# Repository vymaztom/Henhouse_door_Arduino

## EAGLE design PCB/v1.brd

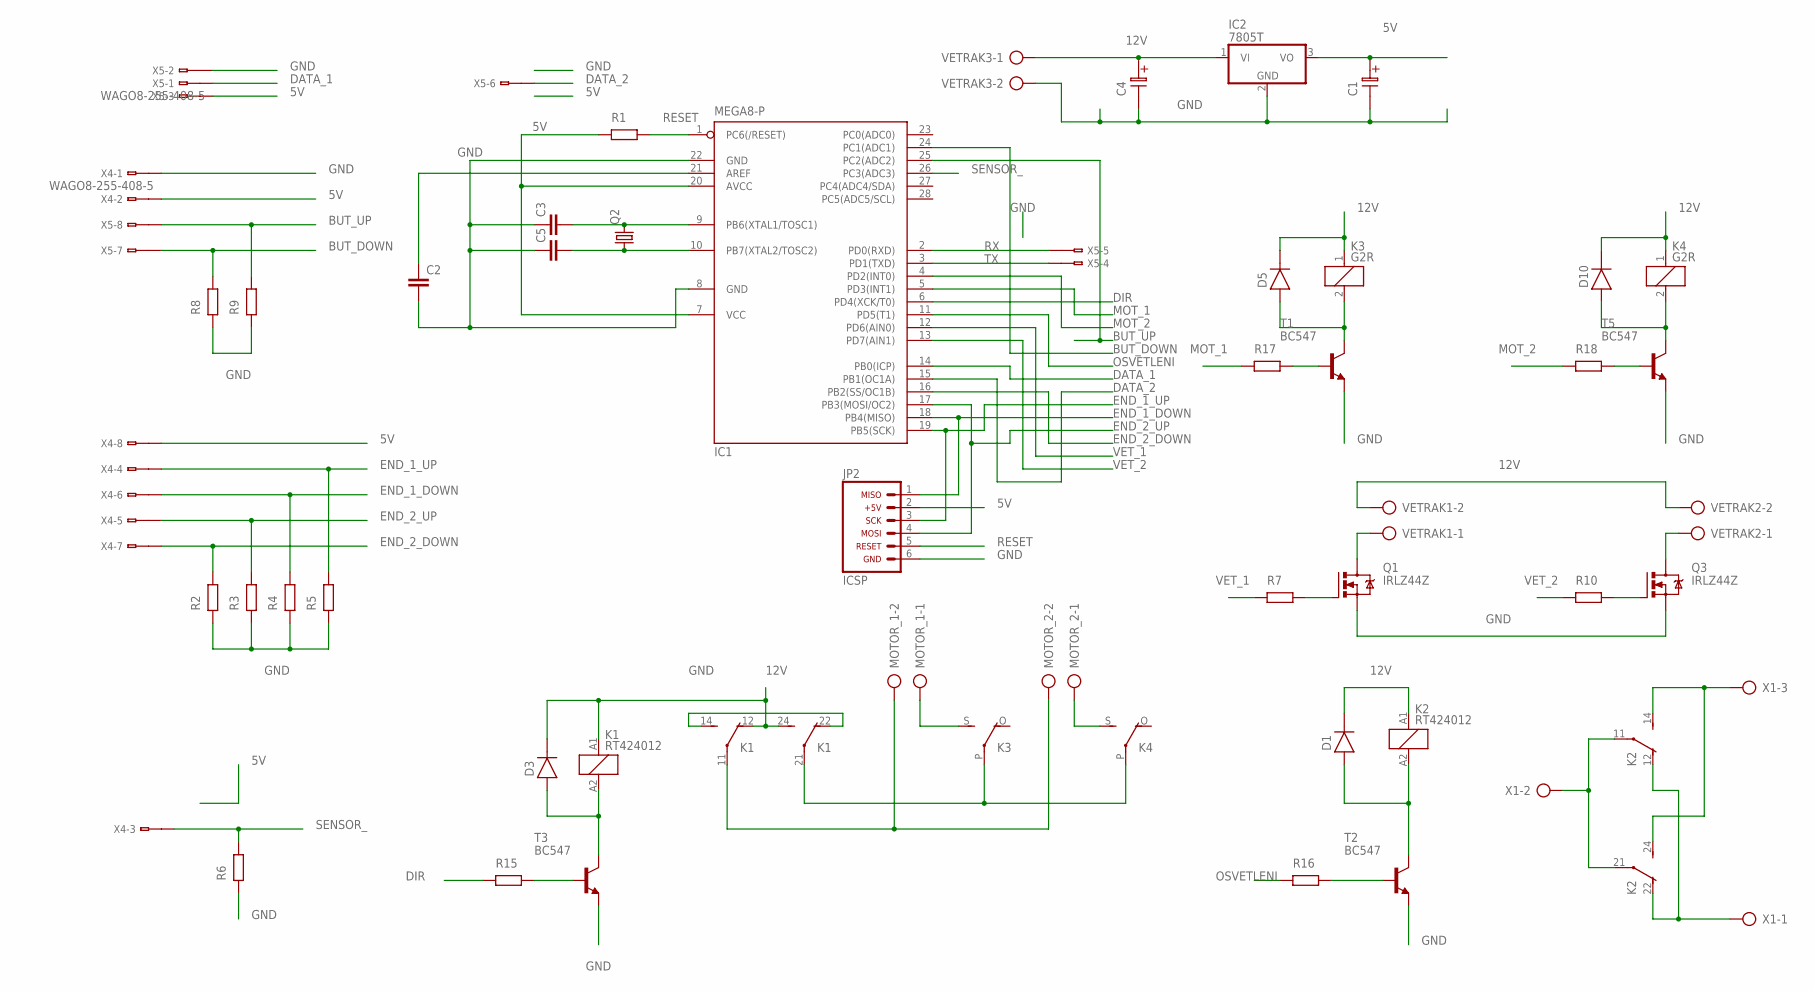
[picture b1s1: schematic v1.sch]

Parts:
C1, C4: CT12
C2: C-EU025-030X050; C025-030X050
C3, C5: C-EU050-025X075; C050-025X075
D1, D3, D5, D10: 1N4007; DO41
IC1: MEGA8-P; DIL28-3
IC2: 7805T; TO220H
JP2: ARDUINO_CONN-ICSP; CONN-2X03
K1, K2: RT424012; RT2C/O
K3, K4: G2R
MOTOR_1, MOTOR_2: AK500/2
Q1, Q3: IRLZ44Z; TO220BH
Q2: CRYSTALHC49S; HC49/S
R1, R2, R3, R4, R5, R6, R7, R8, R9, R10, R15, R16, R17, R18: RR
T1, T2, T3, T5: BC547; TO92
VETRAK1, VETRAK2, VETRAK3: AK500/2
X1: AK500/3-H
X4, X5: WAGO8-255-408-5; 255-408-5

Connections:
5V: C1.1, IC1.7 (VCC), IC1.20 (AVCC), IC2.3 (VO), JP2.2, R1.1, X4.B2 (B1), X4.B8 (B1), X5.B3 (B1)
12V: C4.1, D1.K, D3.K, D5.K, D10.K, IC2.1 (VI), K1.12 (O), K1.24 (S), K1.A1 (1), K2.A1 (1), K3.1, K4.1, VETRAK1.2, VETRAK2.2, VETRAK3.1
BUT_DOWN: IC1.24 (PC1(ADC1)), R8.2, X5.B7 (B1)
BUT_UP: IC1.25 (PC2(ADC2)), R9.2, X5.B8 (B1)
DATA_1: IC1.14 (PB0(ICP)), X5.B1
DATA_2: IC1.15 (PB1(OC1A)), X5.B6 (B1)
DIR: IC1.6 (PD4(XCK/T0)), R15.1
END_1_DOWN: IC1.18 (PB4(MISO)), JP2.1, R4.2, X4.B6 (B1)
END_1_UP: IC1.19 (PB5(SCK)), JP2.3, R5.2, X4.B4 (B1)
END_2_DOWN: IC1.16 (PB2(SS/OC1B)), R2.2, X4.B7 (B1)
END_2_UP: IC1.17 (PB3(MOSI/OC2)), JP2.4, R3.2, X4.B5 (B1)
GND: C1.2, C2.2, C3.1, C4.2, C5.1, IC1.8 (GND), IC1.22 (GND), IC2.2 (GND), JP2.6, K1.14 (S), K1.22 (O), Q1.S, Q3.S, R2.1, R3.1, R4.1, R5.1, R6.1, R8.1, R9.1, T1.1 (E), T2.1 (E), T3.1 (E), T5.1 (E), VETRAK3.2, X4.B1, X5.B2 (B1)
MOT_1: IC1.5 (PD3(INT1)), R17.1
MOT_2: IC1.4 (PD2(INT0)), R18.1
unnamed: D3.A, K1.A2 (2), T3.3 (C)
unnamed: Q3.G, R10.2
unnamed: K1.11, MOTOR_1.2, MOTOR_2.2
unnamed: K1.21, K3.P, K4.P
unnamed: K4.S, MOTOR_2.1
unnamed: K3.S, MOTOR_1.1
unnamed: R18.2, T5.2 (B)
unnamed: R15.2, T3.2 (B)
unnamed: C3.2, IC1.9 (PB6(XTAL1/TOSC1)), Q2.2
unnamed: C5.2, IC1.10 (PB7(XTAL2/TOSC2)), Q2.1
unnamed: D10.A, K4.2, T5.3 (C)
unnamed: D5.A, K3.2, T1.3 (C)
unnamed: R17.2, T1.2 (B)
unnamed: K2.12 (O), K2.22 (O), X1.1
unnamed: D1.A, K2.A2 (2), T2.3 (C)
unnamed: K2.14 (S), K2.24 (S), X1.3
unnamed: Q1.G, R7.2
unnamed: C2.1, IC1.21 (AREF)
unnamed: R16.2, T2.2 (B)
unnamed: Q3.D, VETRAK2.1
unnamed: Q1.D, VETRAK1.1
unnamed: K2.11, K2.21, X1.2
OSVETLENI: IC1.11 (PD5(T1)), R16.1
RESET: IC1.1 (PC6(/RESET)), JP2.5, R1.2
RX: IC1.2 (PD0(RXD)), X5.B5 (B1)
SENSOR_: IC1.26 (PC3(ADC3)), R6.2, X4.B3 (B1)
TX: IC1.3 (PD1(TXD)), X5.B4 (B1)
VET_1: IC1.12 (PD6(AIN0)), R7.1
VET_2: IC1.13 (PD7(AIN1)), R10.1

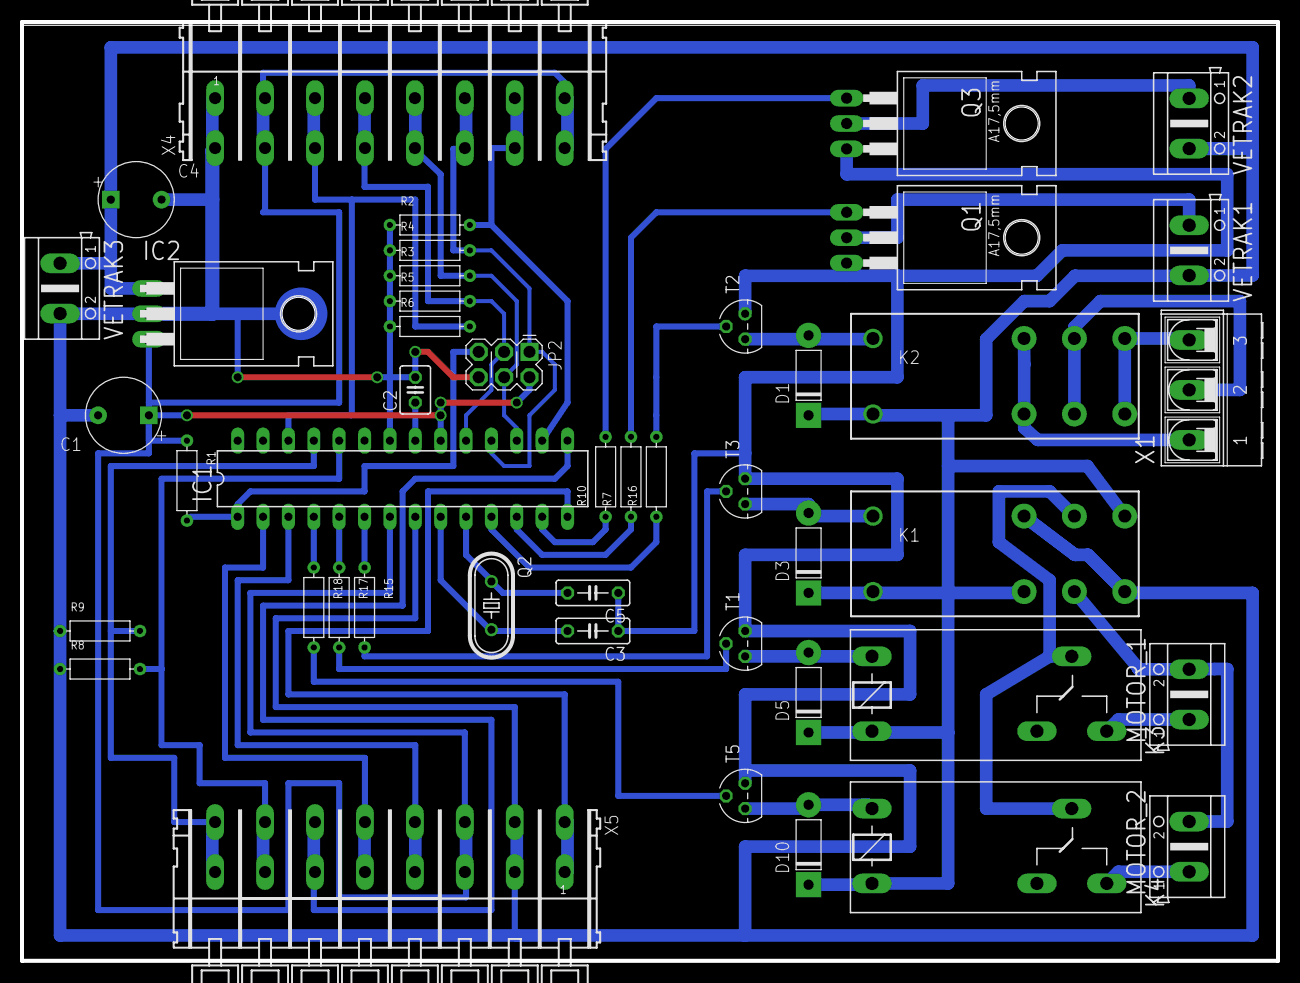
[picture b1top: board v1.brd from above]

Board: 2 copper layers, 125.7 x 94.0 mm, 45 parts (0 on the bottom side), 43 nets.

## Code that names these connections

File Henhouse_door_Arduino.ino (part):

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#define min(X, Y)  ((X) < (Y) ? (X) : (Y))
#define max(X, Y)  ((X) < (Y) ? (Y) : (X))

#define SENSOR A3
#define BUT_UP  A2
#define BUT_DOWN A1


#define MOT_1 3
#define MOT_2 2
#define MOT_DIR 4

#define LED_PIN 5
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#define FAN_1 6
#define FAN_2 7

#define DATA_1 8
#define DATA_2 9

#define END_2_UP 11
#define END_2_DOWN 10
#define END_1_UP 13
#define END_1_DOWN 12

const char text_0[] PROGMEM = ">";
const char text_1[] PROGMEM = "help                      -- print help menu\r\n";
const char text_2[] PROGMEM = "sensor                    -- return actual value of intensity\r\n";
const char text_3[] PROGMEM = "info                      -- print info about device\r\n";
const char text_4[] PROGMEM = "intensity UP <NUMBER>     -- set int number for intensity from range 0-1023\r\n";
const char text_5[] PROGMEM = "time <NUMBER>             -- set int number for time delay from range 0-1023\r\n";
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const char text_7[] PROGMEM = "motor down                -- move down\r\n";
const char text_8[] PROGMEM = "motor end                 -- stop motor move\r\n";
const char text_9[] PROGMEM = "button null               -- set BUTTON to NONE\r\n";
const char text_10[] PROGMEM = "temperature on            -- set temperature sensor ON\r\n";
const char text_11[] PROGMEM = "temperature off           -- set temperature sensors OFF\r\n";
const char text_12[] PROGMEM = "fan <NUMBER> on           -- set fan by NUMBER on\r\n";
const char text_13[] PROGMEM = "fan <NUMBER> off          -- set fan by NUMBER off\r\n";
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	/******************* SET PINS *************************/

	//OUTPUTs
	pinMode(MOT_1, OUTPUT);
	pinMode(MOT_2, OUTPUT);
	pinMode(MOT_DIR, OUTPUT);
	pinMode(LED_PIN, OUTPUT);
	pinMode(FAN_1, OUTPUT);
	pinMode(FAN_2, OUTPUT);

	// END INPUT
	pinMode(END_2_UP, INPUT);
	pinMode(END_2_DOWN, INPUT);
	pinMode(END_1_UP, INPUT);
	pinMode(END_1_DOWN, INPUT);

	// SET VALUE
	digitalWrite(MOT_1,0);
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
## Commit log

2021-08-18 add PCB desk

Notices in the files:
parts and their libraries:
Copyright (C) Vlada 2004-2005
